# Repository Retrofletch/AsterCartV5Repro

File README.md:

Reproduction of a homemade cartridge i got a while simply named the "Astercart rev5" I found another person with a similar cart on Twitter ( @retroWizzard ) who gave me the romdump from his cartridge. 

Because i liked this cartridge and figured others probably would aswell i decided to make a resproduction  of it.

Changes i made was removd 2 IC pads that was not used and i added a jumper header to choose between using my 27C801 multicart ROM and @RetroWizzards 27C1001 Giana Sisters rom. I also added a LED and a Reset button.

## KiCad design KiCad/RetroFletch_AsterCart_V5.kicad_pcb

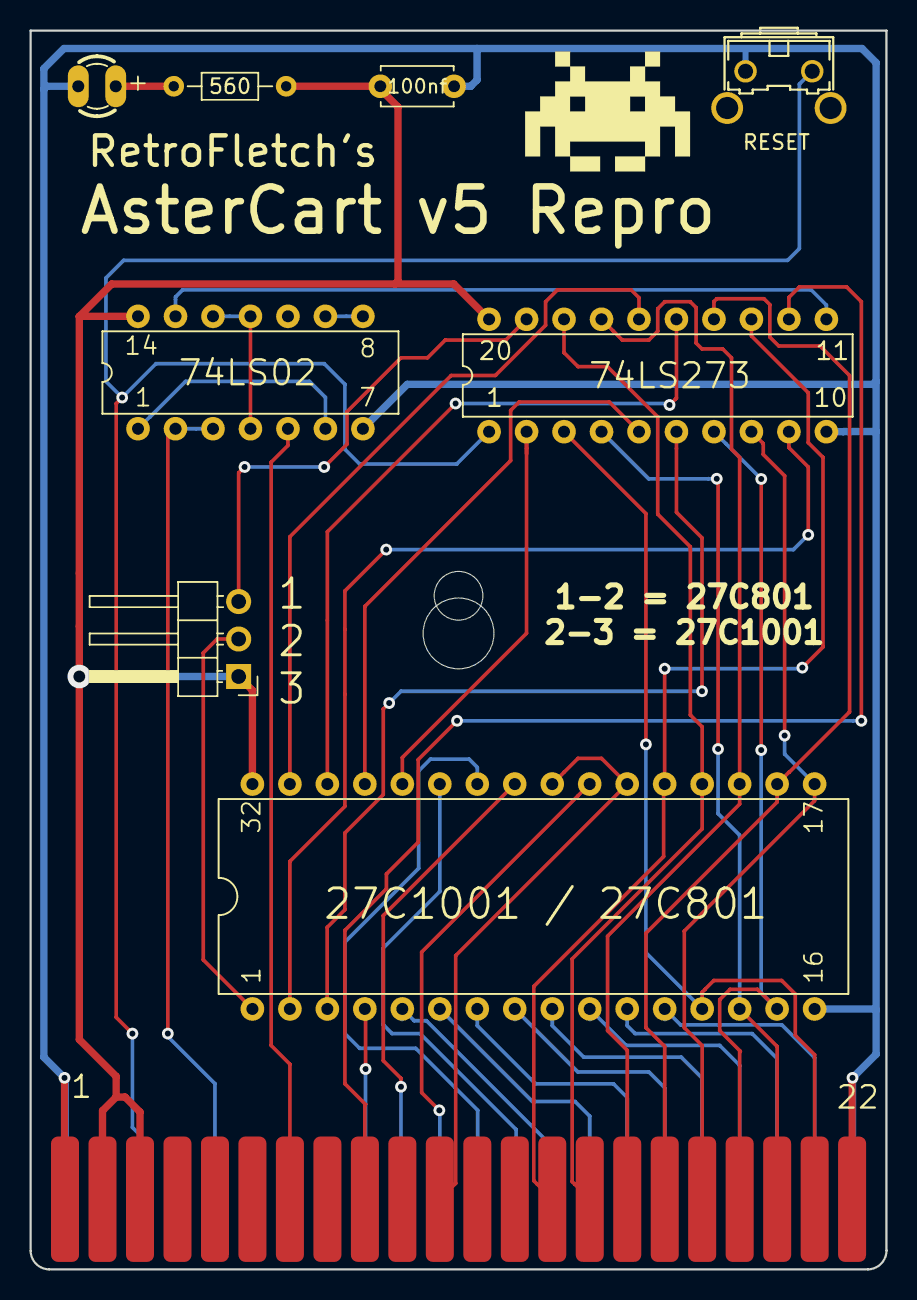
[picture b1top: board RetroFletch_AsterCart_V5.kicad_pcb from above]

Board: 2 copper layers, 58.0 x 84.0 mm, 9 parts (0 on the bottom side), 33 nets.

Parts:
74LS02: 74LS02; DIL14
74LS273: 74LS273; DIL20
100nf: C_Disc_D4.7mm_W2.5mm_P5.00mm
+: LED3E
@HOLE0, @HOLE1: (no value)
RESET: B3F-31XX
U$1: 27C020; DIL32
U$2: C64_EXPANSION; EDGE44_254

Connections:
/+5V: 74LS02.14, 74LS273.20, 100nf.1, U$1.32, U$2.P$2, U$2.P$3
/CD0: 74LS273.3, U$1.13, U$2.P$21
/CD1: 74LS273.4, U$1.14, U$2.P$20
/CD2: 74LS273.7, U$1.15, U$2.P$19
/CD3: 74LS273.8, U$1.17, U$2.P$18
/CD4: 74LS273.14, U$1.18, U$2.P$17
/CD5: 74LS273.17, U$1.19, U$2.P$16
/CD6: 74LS273.18, U$1.20, U$2.P$15
/CD7: 74LS273.13, U$1.21, U$2.P$14
/IO1: 74LS02.5, U$2.P$7
/O2: 74LS02.2, 74LS02.3, U$2.E
/~EXROM: 74LS273.12, U$2.P$9
/~RESET: 74LS273.1, RESET.1, U$2.C
/~ROML: U$1.22, U$1.24, U$2.P$11
GND: 74LS02.7, 74LS273.10, 100nf.2, +.K, RESET.2, U$1.16, U$2.A, U$2.P$1, U$2.P$22, U$2.Z
unnamed: 74LS273.9, U$1.2
unnamed: 74LS273.6, U$1.3
unnamed: U$1.4, U$2.K
unnamed: U$1.5, U$2.R
unnamed: U$1.6, U$2.S
unnamed: U$1.7, U$2.T
unnamed: U$1.8, U$2.U
unnamed: U$1.9, U$2.V
unnamed: U$1.10, U$2.W
unnamed: U$1.11, U$2.X
unnamed: U$1.12, U$2.Y
unnamed: U$1.23, U$2.M
unnamed: U$1.25, U$2.L
unnamed: U$1.26, U$2.N
unnamed: U$1.27, U$2.P
unnamed: 74LS273.5, U$1.29
unnamed: 74LS273.15, U$1.30
unnamed: 74LS273.16, U$1.31

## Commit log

2020-09-28 idontknow
